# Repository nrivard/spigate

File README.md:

# SPI Gate

An SPI controller for homebrew computers done entirely in discrete logic

## What is it?

SPI Gate is a discrete SPI controller intended to be used with homebrew (or real brew) 8- and 16-bit computers.
Typically, retro computers "bit-bang" an SPI interface, manually controlling GPIO pins, usually with something like a 6522 VIA, but this is slow and cumbersome.
Instead, it would be nice to have a programming model similar to an AVR: some memory-mapped registers and set-and-forget data transfer.

## Why is it?

In the end, the real purpose of this device is to enable fast and easy SD card access for a wide range of retro computers, but staying true to a through-hole component aesthetic.
Could this be done in a microcontroller, like an AVR?
Yes.
Could this be done in an FPGA/CPLD?
Yes.
Can many of the basic gates be combined in a GAL?
Again, yes.
And maybe some day I will add those as options.
But the purpose of this particular project is to create a fast, pleasant to use device using *discrete components* to learn how it was done in ye olden dayes.

## Where does it fit?

While the intention of this device is adaptability to a number of retrocomputers, the schematic and PCB is for a 6502-based computer.
Specifically, my homebrew [n8 Bit Special computer](https://github.com/nrivard/n8-Bit).
Adapting it for your 6502 (and hopefully 68000-based as I have a homebrew design) computer should be relatively simple.
The external signal requirements are intentionally pretty light, but this means you may have to change timing if your CPU samples data differently than a 6502.

## How is it supposed to work?

As stated in a previous section, I want it to look very similar to an AVR's SPI function:

* a memory-mapped control register
* a memory-mapped data register
* polling or interrupt when all 8 bits have been transferred
* programmable clock speed

But this is going in a retrocomputer, so the device also needs:
* device-select lines (to free up the computer's GPIO lines or remove the need for them entirely)

And lastly, intended purpose is for an SD card, and so to reduce complexity, it will be:
* Mode 0 only
* shift MSB only
* no write-collision detection (you should be careful!)

### External Signals

The following are the external signals that interface with the computer:

| Signal | I/O? | Description |
| --- | --- | --- |
| D0..7 | In-out | 8 bit data bus |
| A0 | Input | 1 bit register select |
| CLK | Input | System clock |
| RW | Input | Read when high, write when low |
| /CE | Input | Device selected when low |
| /RES | Input | Reset when low |
| /IRQ | Output | Transmission complete when low and interrupts enabled |

The following are external signals that interface with SPI devices:

| Signal | I/O? | Description |
| --- | --- | --- |
| SCLK | Output | SPI Clock |
| MOSI | Output | Serial output to device |
| MISO | Input | Serial input from device |
| /CS0..3 | Output | Device select lines, low is assertion |

_Note: a `/` prefix indicates that signal is active-low_

### Control Register

The control register is an 8-bit register that looks like:

| Bit 7 | 	Bit 6 |	Bit 5 |	Bit 4 |	Bit 3 |	Bit 2 |	Bit 1 |	Bit 0 |
| ---   | ---     | ---   | ---   | ---   | ---   | ---   | --- |
| ITC | BUSY | IEN | DEN | SEL1 | SEL0 | DIV1 | DIV0 |

DIV0 and DIV1 form a 2 bit clock divider select with the following possible values:

| SPI1 | SPI0 | Clock Divide |
| - | - | - |
| 0 | 0 | CLK / 2 |
| 0 | 1 | CLK / 8 |
| 1 | 0 | CLK / 16 |
| 1 | 1 | CLK / 32 |

There is no way to run this device at full CPU speed, it will always be divided in some way.
Taking the default clock rate of the n8 Bit computer (~3.6Mhz) you can select from speeds of 1.8Mhz, 450khz, 225khz, and 112khz.
This is important because certain devices will not operate at too high a clock speed.
SD cards, for example, require a clock speed between 100khz and 400khz to enter SPI mode.

SEL0 and SEL1 form a 2 bit device select.
`00` will select device 1, `01` will select device 2, and so on.

DEN is a Device Enable bit.
When on, whatever device is selected via SEL0 and SEL1 will be enabled. When off, no SPI device's CS line will be asserted.

IEN is an Interrupt Enable bit. When on, the /IRQ line will be asserted when a transfer has completed.

BUSY is a status flag.
When on, it means a transfer is in progress.
You can use this to avoid write-collisions.

ITC is the Interrupt/Transfer Complete flag.
When a transfer is complete, this bit will be asserted and can be polled in a loop or tested in an interrupt handler.
To clear the ITC flag, a read or a write must be made to the data register.

### Data Register

The data register is an 8 bit register.
Data transfer is initiated on a write and is performed independently from the system.
The result of the transfer from the SPI device is stored in the register.
Reading or writing this register will reset the ITC flag in the control register.

## What does it look like?

The design uses 12 74HC series chips:

| Chip | Count | Description |
| --- | --- | --- |
| 74HC273 | 1 | 8-bit register |
| 74HC74 | 1 | Dual flip-flop |
| 74HC245 | 1 | 8 bit bus transceiver |
| 74HC165 | 1 | Parallel-in, serial-out shift register |
| 74HC595 | 1 | Serial-in, parallel-out shift register |
| 74HC393 | 2 | Dual 4-bit binary counter |
| 74HC153 | 1 | Dual 4 input multiplexer |
| 74HC139 | 1 | Dual 2-to-4 decoder |
| 74HC00 | 1 | Quad-NAND gate |
| 74HC04 | 1 | Hex-NOT gate |
| 74HC08 | 1 | Quad-AND gate |

The design is relatively efficient, with only a single AND gate, a single NOT gate, and 1 of the counters being un-utilized.
The [schematic](spigate_schem.pdf) is organized into subsystems as much as possible and the PCB has some of the higher level functions marked on the silkscreen.

## Testing

2 levels of testing were done to verify the design.

### Digital Simulation

The first level of testing was done using [Digital](https://github.com/hneemann/Digital).

To run the simulation, open [SPIGate.dig](digital/SPIGate.dig) in Digital.
It's helpful to run it in stepping mode so you can synchronize signals to occur at the same time, which is closer to how it actually runs on a computer.

### Breadboarding

After the design was verified in simulation, I implemented it on a breadboard and connected it to my real computer.

It was connected to a real SD card and communication was verified using a logic analyzer.

### PCB

A PCB was designed and ordered but has not been tested yet.

## What about other computers?

SPI Gate was designed to easily integrate into a 6502-based design.
You should be able to hook the following signals up directly: CLK, /RES, RW, D0..7, A0, and /IRQ.

You should only need to generate /CE appropriately.
Note: the design here _qualifies_ /CE with CLK (ie, when /CE is low and CLK is high, device is selected).

If you want to integrate with another type of machine, you may have to change how SPI Gate is selected (maybe changing or removing qualification) so that data is sampled at the correct time.
In this case, care was taken to sample data for a write on the negative edge of the system clock.

If your machine also has separate /RD and /WR signals (like an x86 system), you will have to have some logic to move to the RW signal expected here or adapt the design itself to accommodate separate signals.

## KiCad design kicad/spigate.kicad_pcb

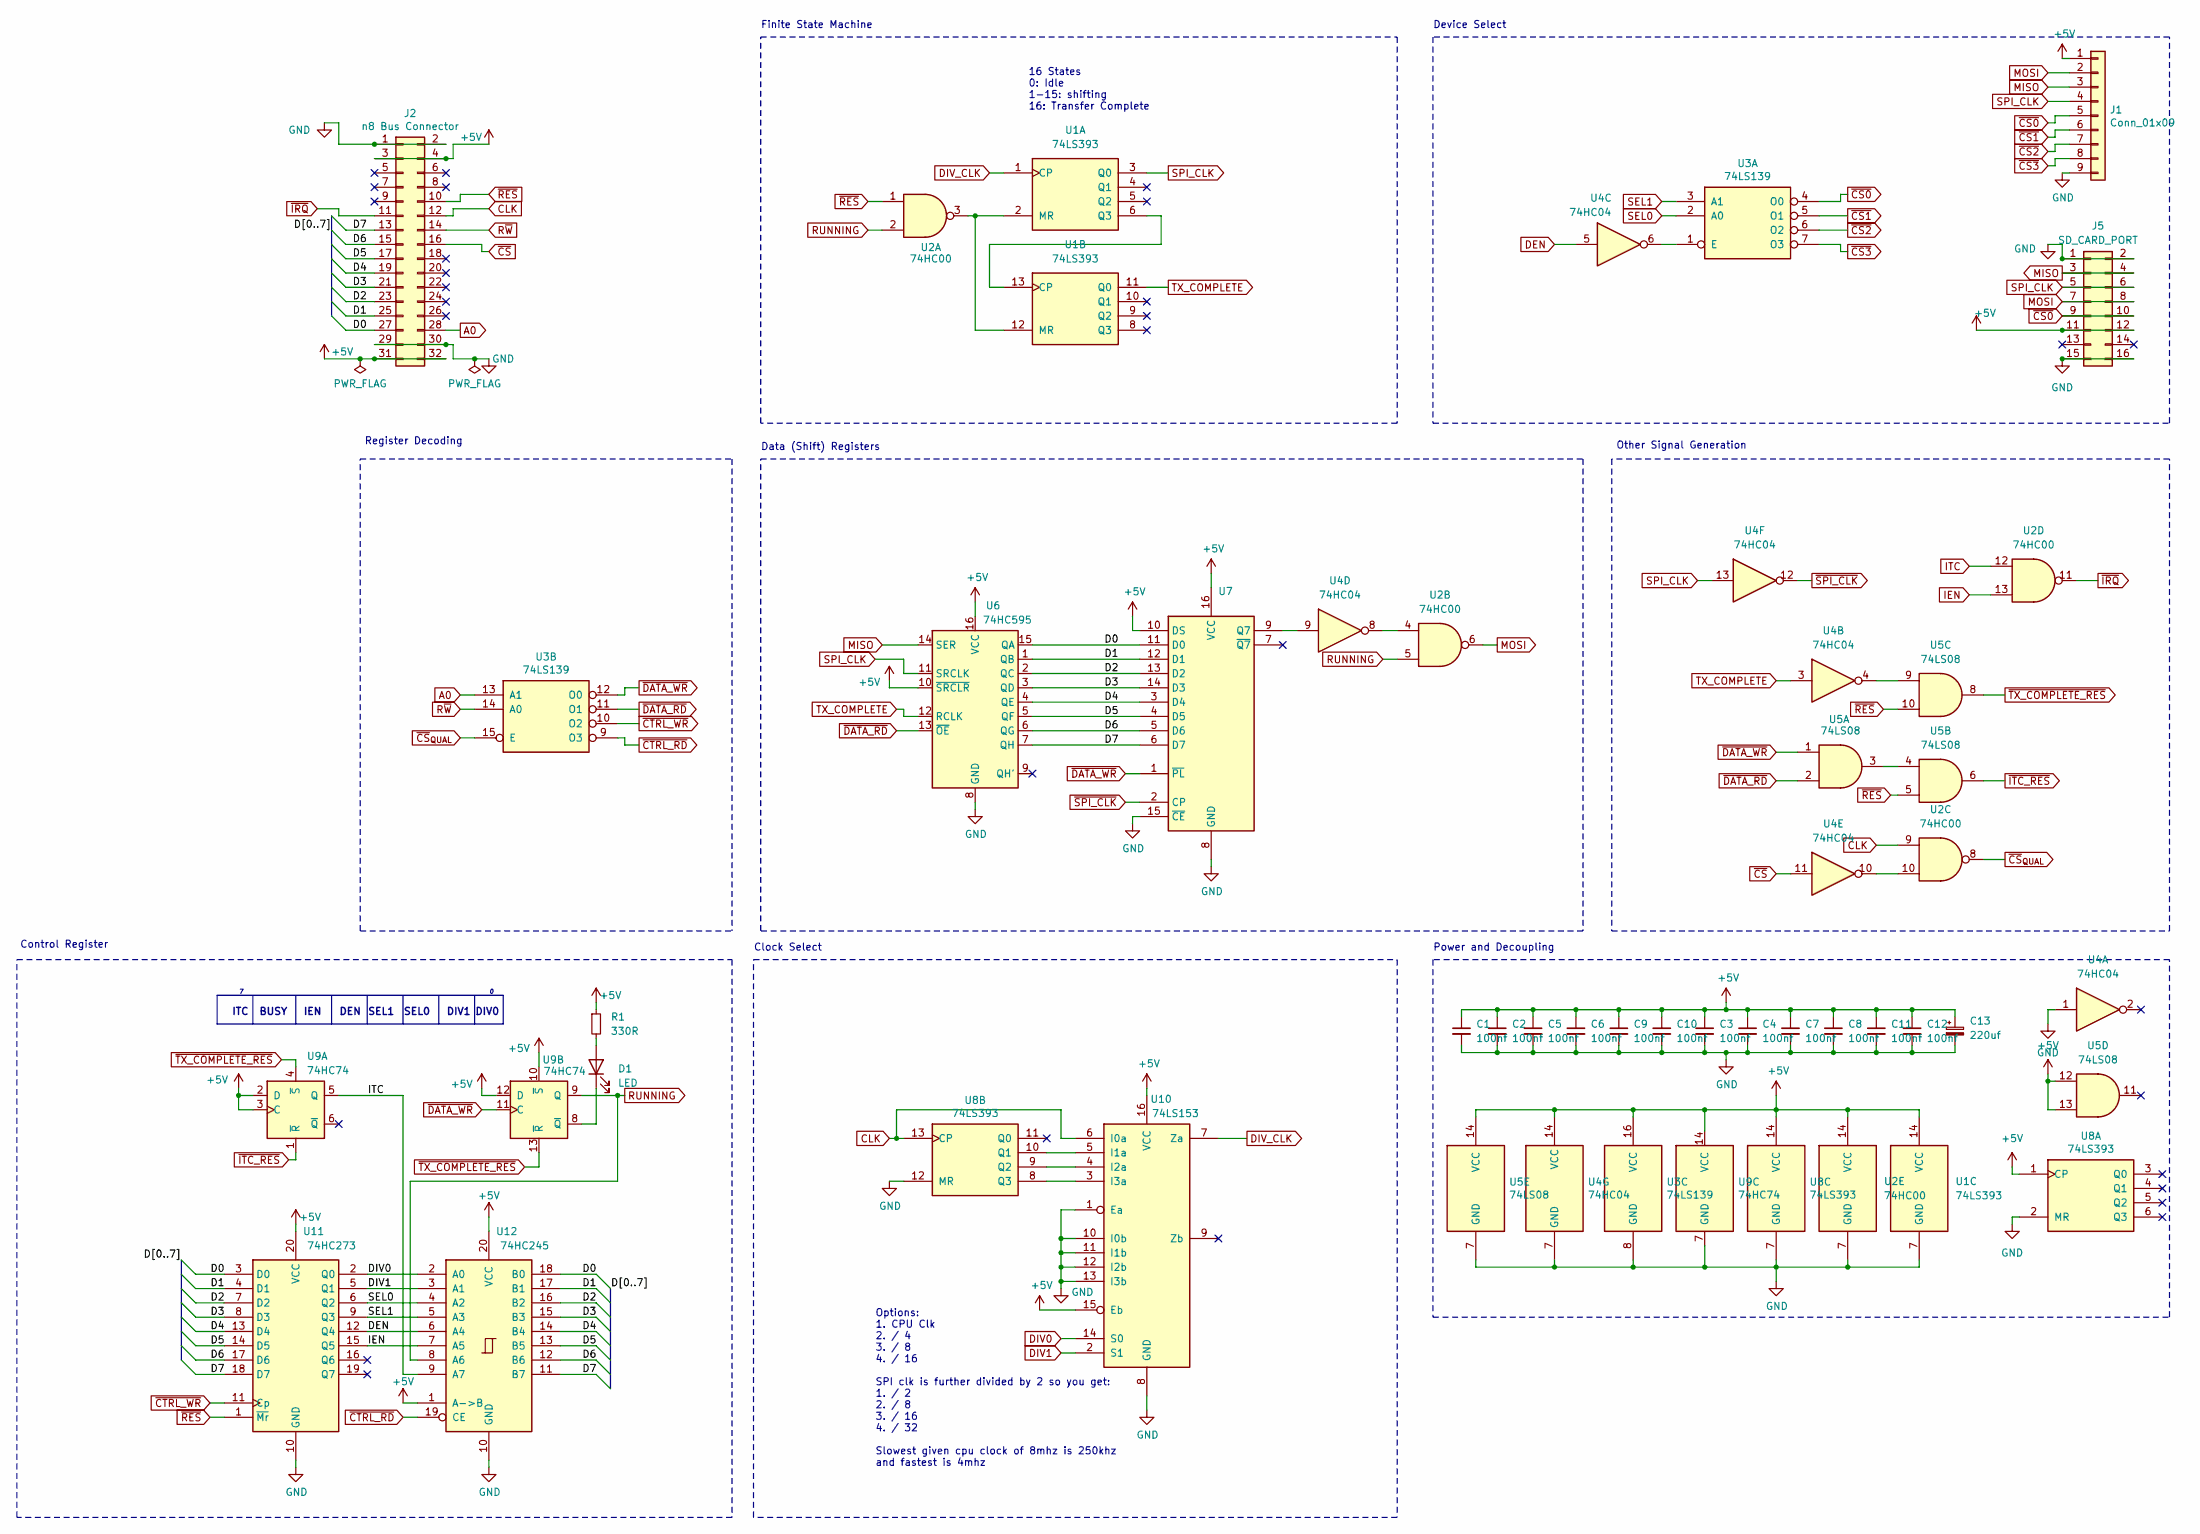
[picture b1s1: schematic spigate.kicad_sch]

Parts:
C1, C2, C3, C4, C5, C6, C7, C8, C9, C10, C11, C12: 100nf; C_Disc_D5.0mm_W2.5mm_P2.50mm
C13: 220uf; CP_Radial_D6.3mm_P2.50mm
D1: LED; LED_0805_2012Metric_Pad1.15x1.40mm_HandSolder
J1: Conn_01x09; PinSocket_1x09_P2.54mm_Horizontal
J2: n8 Bus Connector; PinHeader_2x16_P2.54mm_Horizontal
J5: SD_CARD_PORT; PinSocket_2x08_P2.54mm_Vertical
R1: 330R; R_0805_2012Metric_Pad1.20x1.40mm_HandSolder
U1, U8: 74LS393; DIP-14_W7.62mm_Socket
U2: 74HC00; DIP-14_W7.62mm_Socket
U3: 74LS139; DIP-16_W7.62mm_Socket
U4: 74HC04; DIP-14_W7.62mm_Socket
U5: 74LS08; DIP-14_W7.62mm_Socket
U6: 74HC595; DIP-16_W7.62mm_Socket
U7: 74HC165; DIP-16_W7.62mm_Socket
U9: 74HC74; DIP-14_W7.62mm_Socket
U10: 74LS153; DIP-16_W7.62mm_Socket
U11: 74HC273; DIP-20_W7.62mm_Socket
U12: 74HC245; DIP-20_W7.62mm_Socket

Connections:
/D0: J2.27, U6.15 (QA), U7.11 (D0), U11.3 (D0), U12.18 (B0)
/D1: J2.25, U6.1 (QB), U7.12 (D1), U11.4 (D1), U12.17 (B1)
/D2: J2.23, U6.2 (QC), U7.13 (D2), U11.7 (D2), U12.16 (B2)
/D3: J2.21, U6.3 (QD), U7.14 (D3), U11.8 (D3), U12.15 (B3)
/D4: J2.19, U6.4 (QE), U7.3 (D4), U11.13 (D4), U12.14 (B4)
/D5: J2.17, U6.5 (QF), U7.4 (D5), U11.14 (D5), U12.13 (B5)
/D6: J2.15, U6.6 (QG), U7.5 (D6), U11.17 (D6), U12.12 (B6)
/D7: J2.13, U6.7 (QH), U7.6 (D7), U11.18 (D7), U12.11 (B7)
A0: J2.28, U3.13 (A1)
CLK: J2.12, U2.9, U8.13 (CP), U10.6 (I0a)
DEN: U4.5, U11.12 (Q4), U12.6 (A4)
DIV0: U10.14 (S0), U11.2 (Q0), U12.2 (A0)
DIV1: U10.2 (S1), U11.5 (Q1), U12.3 (A1)
DIV_CLK: U1.1 (CP), U10.7 (Za)
GND: C1.2, C2.2, C3.2, C4.2, C5.2, C6.2, C7.2, C8.2, C9.2, C10.2, C11.2, C12.2, C13.2, J1.9, J2.1, J2.2, J2.29, J2.30, J5.1, J5.2, J5.15, J5.16, U1.7 (GND), U2.7 (GND), U3.8 (GND), U4.1, U4.7 (GND), U5.7 (GND), U6.8 (GND), U7.8 (GND), U7.15 (~CE), U8.2 (MR), U8.7 (GND), U8.12 (MR), U9.7 (GND), U10.1 (Ea), U10.8 (GND), U10.10 (I0b), U10.11 (I1b), U10.12 (I2b), U10.13 (I3b), U11.10 (GND), U12.10 (GND)
IEN: U2.13, U11.15 (Q5), U12.7 (A5)
ITC: U2.12, U9.5 (Q), U12.9 (A7)
MISO: J1.3, J5.3, J5.4, U6.14 (SER)
MOSI: J1.2, J5.7, J5.8, U2.6
unnamed: D1.2 (A), R1.2
unnamed: D1.1 (K), U9.8 (~Q)
unnamed: U1.2 (MR), U1.12 (MR), U2.3
unnamed: U1.6 (Q3), U1.13 (CP)
unnamed: U2.4, U4.8
unnamed: U2.10, U4.10
unnamed: U3.1 (E), U4.6
unnamed: U4.4, U5.9
unnamed: U5.3, U5.4
unnamed: U4.9, U7.9 (Q7)
unnamed: U8.10 (Q1), U10.5 (I1a)
unnamed: U8.9 (Q2), U10.4 (I2a)
unnamed: U8.8 (Q3), U10.3 (I3a)
RUNNING: U2.2, U2.5, U9.9 (Q), U12.8 (A6)
R~W: J2.14, U3.14 (A0)
SEL0: U3.2 (A0), U11.6 (Q2), U12.4 (A2)
SEL1: U3.3 (A1), U11.9 (Q3), U12.5 (A3)
SPI_CLK: J1.4, J5.5, J5.6, U1.3 (Q0), U4.13, U6.11 (SRCLK)
TX_COMPLETE: U1.11 (Q0), U4.3, U6.12 (RCLK)
~CS0: J1.5, J5.9, J5.10, U3.4 (O0)
~CS1: J1.6, U3.5 (O1)
~CS2: J1.7, U3.6 (O2)
~CS3: J1.8, U3.7 (O3)
~CS: J2.16, U4.11
~CS_{QUAL}: U2.8, U3.15 (E)
~CTRL_RD: U3.9 (O3), U12.19 (CE)
~CTRL_WR: U3.10 (O2), U11.11 (Cp)
~DATA_RD: U3.11 (O1), U5.2, U6.13 (~OE)
~IRQ: J2.11, U2.11
~ITC_RES: U5.6, U9.1 (~R)
~RES: J2.10, U2.1, U5.5, U5.10, U11.1 (~Mr)
~SPI_CLK: U4.12, U7.2 (CP)
~TX_COMPLETE_RES: U5.8, U9.4 (~S), U9.13 (~R)

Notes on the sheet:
Clock Select
ITC
Control Register
DEN
Other Signal Generation
Finite State Machine
IEN
SEL0
Power and Decoupling
DIV1
Device Select
Options: 1. CPU Clk 2. / 4 3. / 8 4. / 16 SPI clk is further divided by 2 so you get: 1. / 2 2. / 8 3. / 16 4. / 32 Slowest given cpu clock of 8mhz is 250khz and fastest is 4mhz
Register Decoding
Data (Shift) Registers
SEL1
16 States 0: Idle 1-15: shifting 16: Transfer Complete
DIV0
BUSY

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
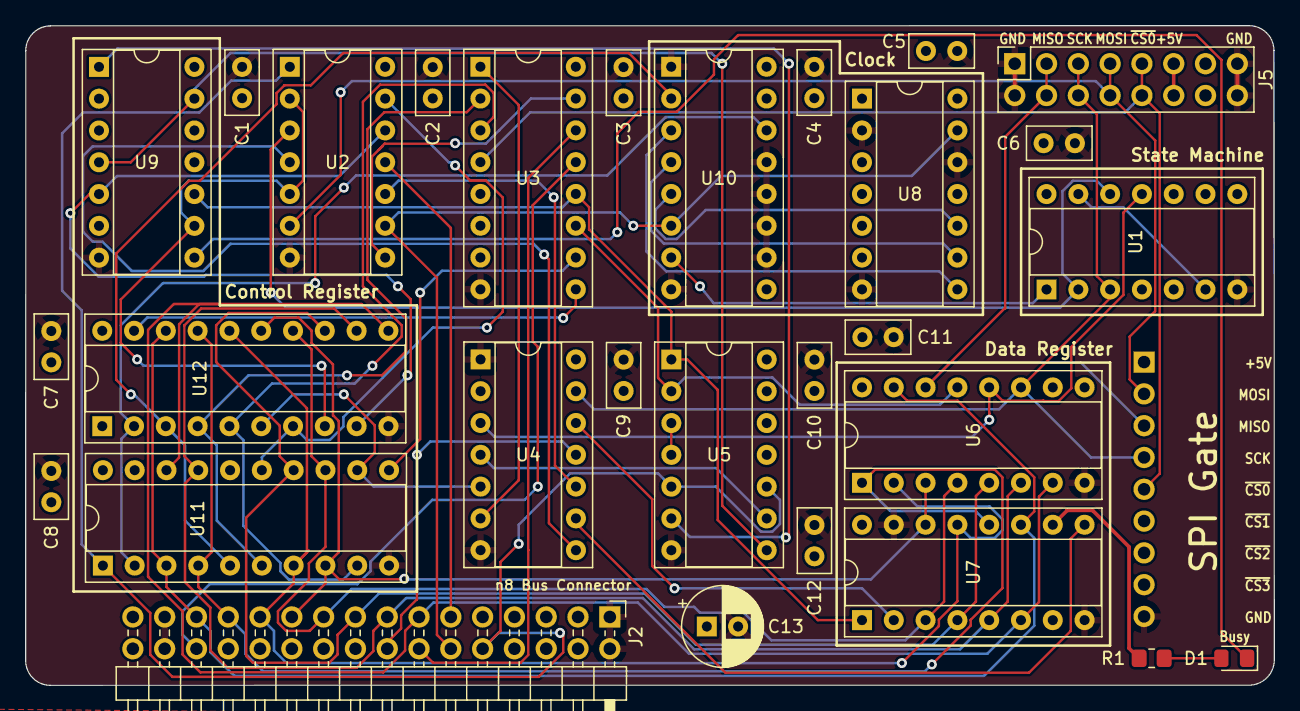
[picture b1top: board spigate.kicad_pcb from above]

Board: 4 copper layers, 99.7 x 52.7 mm, 30 parts (1 on the bottom side), 54 nets.

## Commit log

2024-11-05 Added schematic and digital simulation Updated README
2024-11-05 removed references to the old name
2024-11-05 removed backup files with old name e Please enter the commit message for your changes. Lines starting
2024-11-05 RC1 complete
2025-07-02 shipped board
